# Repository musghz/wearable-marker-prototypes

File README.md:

# wearable-marker-prototypes

Wearable markers for motion capture using a webcam

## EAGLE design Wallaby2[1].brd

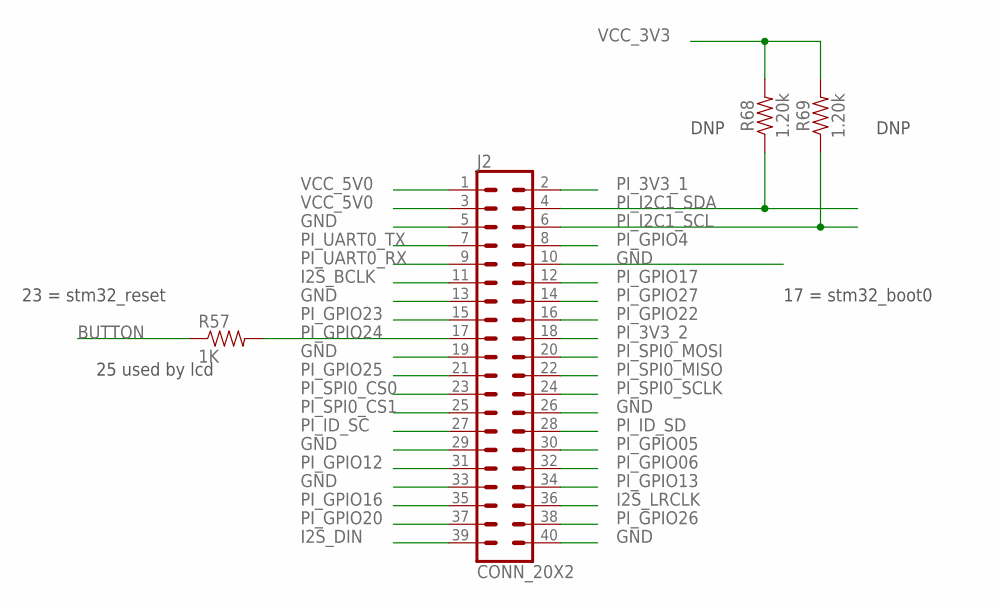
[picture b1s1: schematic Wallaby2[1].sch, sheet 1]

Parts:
J2: CONN_20X2; 2X20
R57: 1K; 0603-RES
R68, R69: 1.20k; 0603

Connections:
BUTTON: R57.1; also elsewhere on the board
GND: J2.5, J2.10, J2.13, J2.19, J2.26, J2.29, J2.33, J2.40; also elsewhere on the board
I2S_BCLK: J2.11; also elsewhere on the board
I2S_DIN: J2.39; also elsewhere on the board
I2S_LRCLK: J2.36; also elsewhere on the board
PI_3V3_1: J2.2
PI_3V3_2: J2.18
PI_GPIO4: J2.8
PI_GPIO05: J2.30
PI_GPIO06: J2.32
PI_GPIO12: J2.31
PI_GPIO13: J2.34
PI_GPIO16: J2.35
PI_GPIO17: J2.12; also elsewhere on the board
PI_GPIO20: J2.37
PI_GPIO22: J2.16
PI_GPIO23: J2.15; also elsewhere on the board
PI_GPIO24: J2.17, R57.2
PI_GPIO25: J2.21; also elsewhere on the board
PI_GPIO26: J2.38
PI_GPIO27: J2.14
PI_I2C1_SCL: J2.6, R69.1; also elsewhere on the board
PI_I2C1_SDA: J2.4, R68.1; also elsewhere on the board
PI_ID_SC: J2.27
PI_ID_SD: J2.28
PI_SPI0_CS0: J2.23; also elsewhere on the board
PI_SPI0_CS1: J2.25
PI_SPI0_MISO: J2.22; also elsewhere on the board
PI_SPI0_MOSI: J2.20; also elsewhere on the board
PI_SPI0_SCLK: J2.24; also elsewhere on the board
PI_UART0_RX: J2.9; also elsewhere on the board
PI_UART0_TX: J2.7; also elsewhere on the board
VCC_3V3: R68.2, R69.2; also elsewhere on the board
VCC_5V0: J2.1, J2.3; also elsewhere on the board

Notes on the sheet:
25 used by lcd
23 = stm32_reset
17 = stm32_boot0
DNP

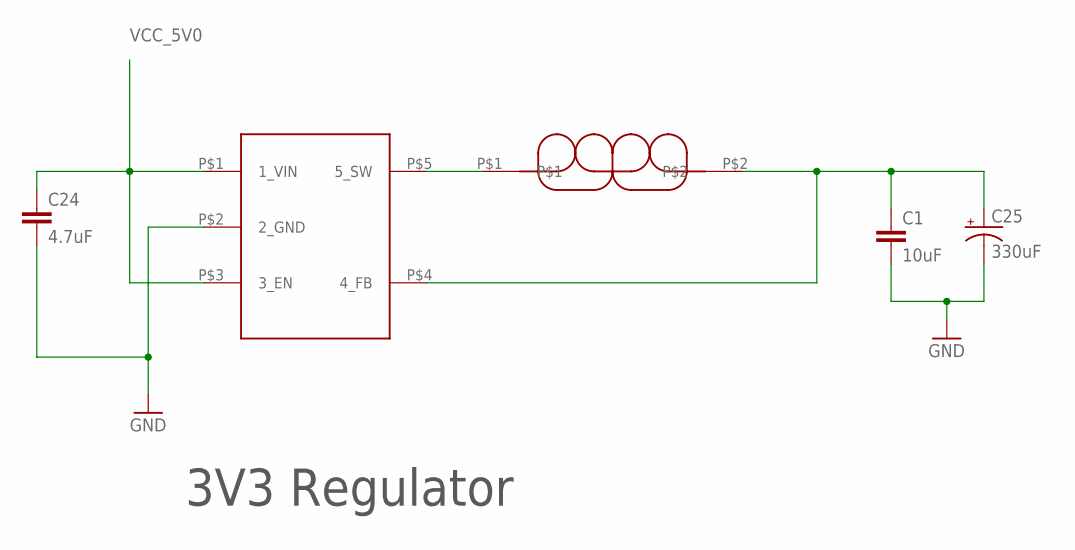
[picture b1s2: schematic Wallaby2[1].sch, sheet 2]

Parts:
C1: 10uF; 0603-CAP
C24: 4.7uF; 0603-CAP
C25: 330uF; PANASONIC_D
U7: LM3671; SOT-23-5
U8: 2.2uH; 3P2MM-X-3P2MM-INDUCTOR

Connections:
GND: C1.2, C24.2, C25.-, U7.P$2 (2_GND); also elsewhere on the board
unnamed: U7.P$5 (5_SW), U8.P$1
VCC_3V3: C1.1, C25.+, U7.P$4 (4_FB), U8.P$2; also elsewhere on the board
VCC_5V0: C24.1, U7.P$1 (1_VIN), U7.P$3 (3_EN); also elsewhere on the board

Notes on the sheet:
3V3 Regulator

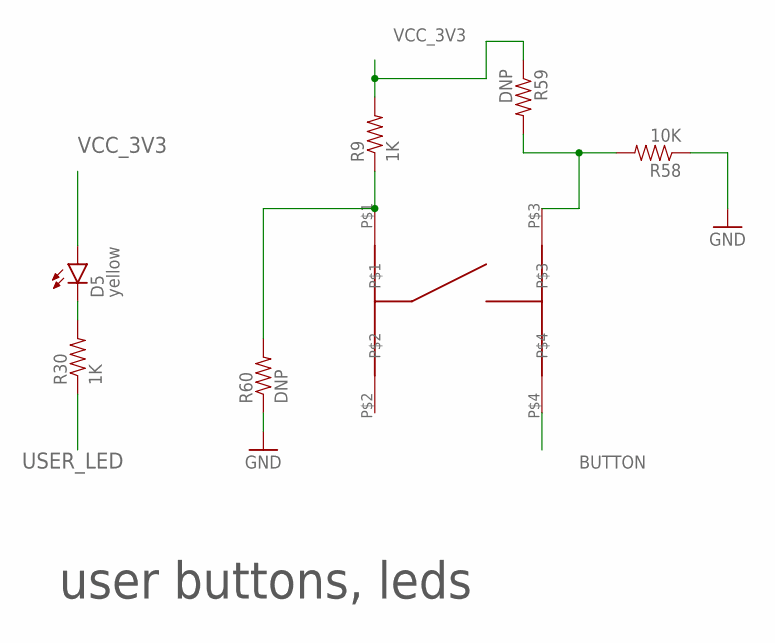
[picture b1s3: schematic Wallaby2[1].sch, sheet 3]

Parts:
D5: yellow; LED-0603
R9, R30: 1K; 0603-RES
R58: 10K; 0603-RES
R59, R60: DNP; 0603-RES
U75: PUSHBUTTON-1571527-2; BUTTON-1571527-2

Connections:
BUTTON: U75.P$4; also elsewhere on the board
GND: R58.1, R60.1; also elsewhere on the board
unnamed: D5.C, R30.2
unnamed: R9.1, R60.2, U75.P$1
unnamed: R58.2, R59.2, U75.P$3
USER_LED: R30.1; also elsewhere on the board
VCC_3V3: D5.A, R9.2, R59.1; also elsewhere on the board

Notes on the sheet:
user buttons, leds

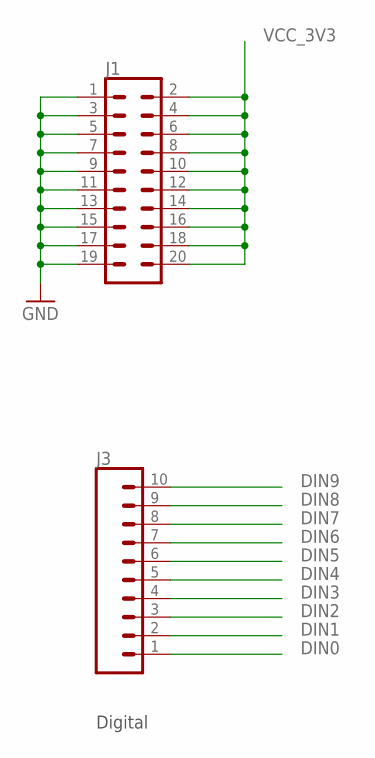
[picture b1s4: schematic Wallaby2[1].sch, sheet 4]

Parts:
J1: CONN_10X2; 2X10
J3: CONN_10"; 1X10

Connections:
DIN0: J3.1; also elsewhere on the board
DIN1: J3.2; also elsewhere on the board
DIN2: J3.3; also elsewhere on the board
DIN3: J3.4; also elsewhere on the board
DIN4: J3.5; also elsewhere on the board
DIN5: J3.6; also elsewhere on the board
DIN6: J3.7; also elsewhere on the board
DIN7: J3.8; also elsewhere on the board
DIN8: J3.9; also elsewhere on the board
DIN9: J3.10; also elsewhere on the board
GND: J1.1, J1.3, J1.5, J1.7, J1.9, J1.11, J1.13, J1.15, J1.17, J1.19; also elsewhere on the board
VCC_3V3: J1.2, J1.4, J1.6, J1.8, J1.10, J1.12, J1.14, J1.16, J1.18, J1.20; also elsewhere on the board

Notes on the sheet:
Digital

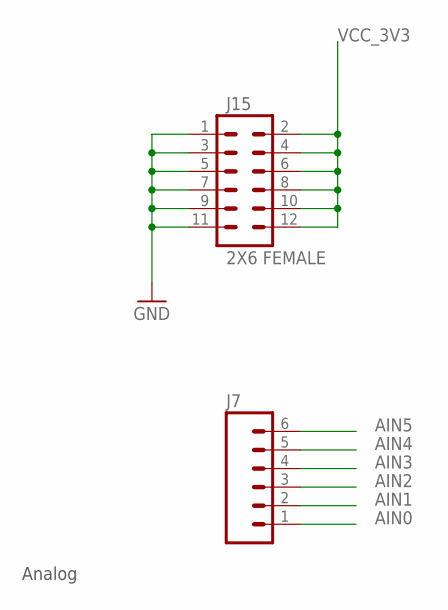
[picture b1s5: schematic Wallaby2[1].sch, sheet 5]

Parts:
J7: M06SILK_FEMALE_PTH; 1X06
J15: 2X6 FEMALE; 2X6

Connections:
AIN0: J7.1; also elsewhere on the board
AIN1: J7.2; also elsewhere on the board
AIN2: J7.3; also elsewhere on the board
AIN3: J7.4; also elsewhere on the board
AIN4: J7.5; also elsewhere on the board
AIN5: J7.6; also elsewhere on the board
GND: J15.1, J15.3, J15.5, J15.7, J15.9, J15.11; also elsewhere on the board
VCC_3V3: J15.2, J15.4, J15.6, J15.8, J15.10, J15.12; also elsewhere on the board

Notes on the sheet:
Analog

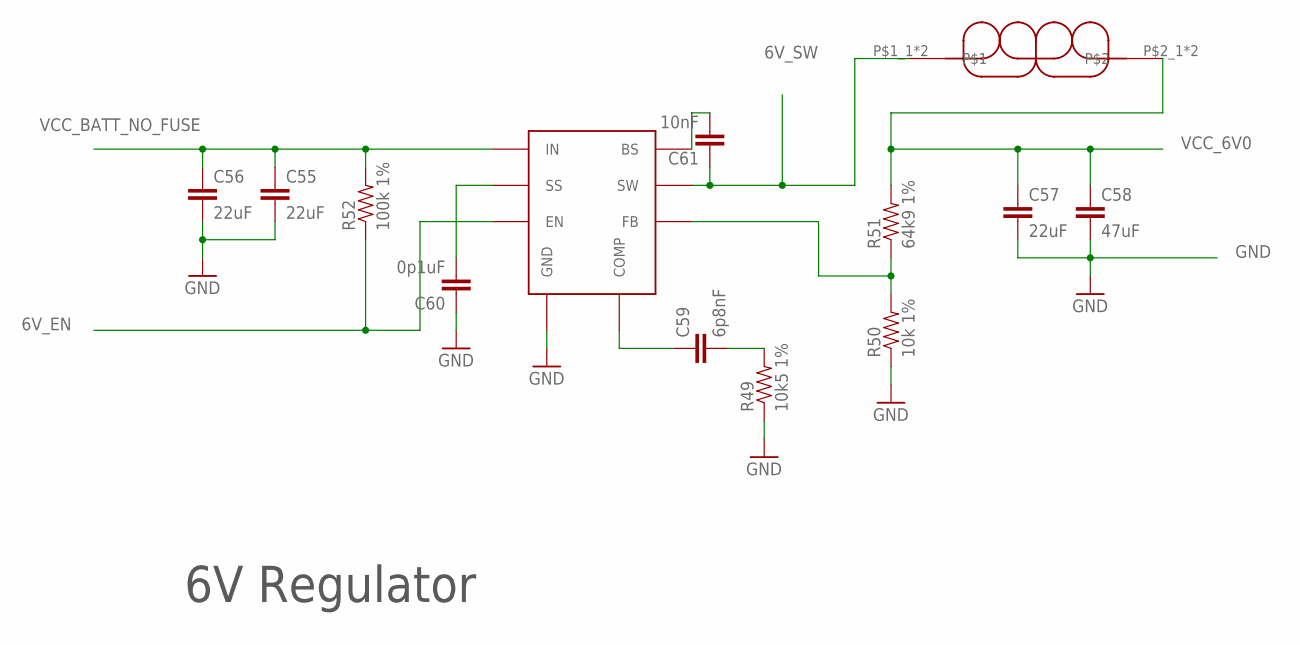
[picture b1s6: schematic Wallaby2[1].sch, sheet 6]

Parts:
C55, C56, C57: 22uF; 1210@1
C58: 47uF; 1210@1
C59: 6p8nF; 0603-CAP
C60: 0p1uF; 0603-CAP
C61: 10nF; 0603-CAP
L2: 6.5uH; INDUCT-3232-1050
R49: 10k5 1%; 0603-RES
R50: 10k 1%; 0603-RES
R51: 64k9 1%; 0603-RES
R52: 100k 1%; 0603-RES
U72: AP65502; SO-8EP

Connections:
6V_EN: R52.1, U72.7 (EN); also elsewhere on the board
6V_SW: C61.1, L2.P$1_1, L2.P$1_2, U72.3 (SW)
GND: C55.2, C56.2, C57.2, C58.2, C60.1, R49.1, R50.1, U72.4 (GND), U72.GND, U72.V$1 (GND), U72.V$2 (GND), U72.V$3 (GND), U72.V$4 (GND), U72.V$5 (GND), U72.V$6 (GND), U72.V$7 (GND), U72.V$8 (GND), U72.V$9 (GND), U72.V$10 (GND), U72.V$11 (GND), U72.V$12 (GND), U72.V$13 (GND), U72.V$14 (GND), U72.V$15 (GND); also elsewhere on the board
unnamed: C61.2, U72.1 (BS)
unnamed: C59.1, U72.6 (COMP)
unnamed: C59.2, R49.2
unnamed: C60.2, U72.8 (SS)
unnamed: R50.2, R51.1, U72.5 (FB)
VCC_6V0: C57.1, C58.1, L2.P$2_1, L2.P$2_2, R51.2; also elsewhere on the board
VCC_BATT_NO_FUSE: C55.1, C56.1, R52.2, U72.2 (IN); also elsewhere on the board

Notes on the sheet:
6V Regulator

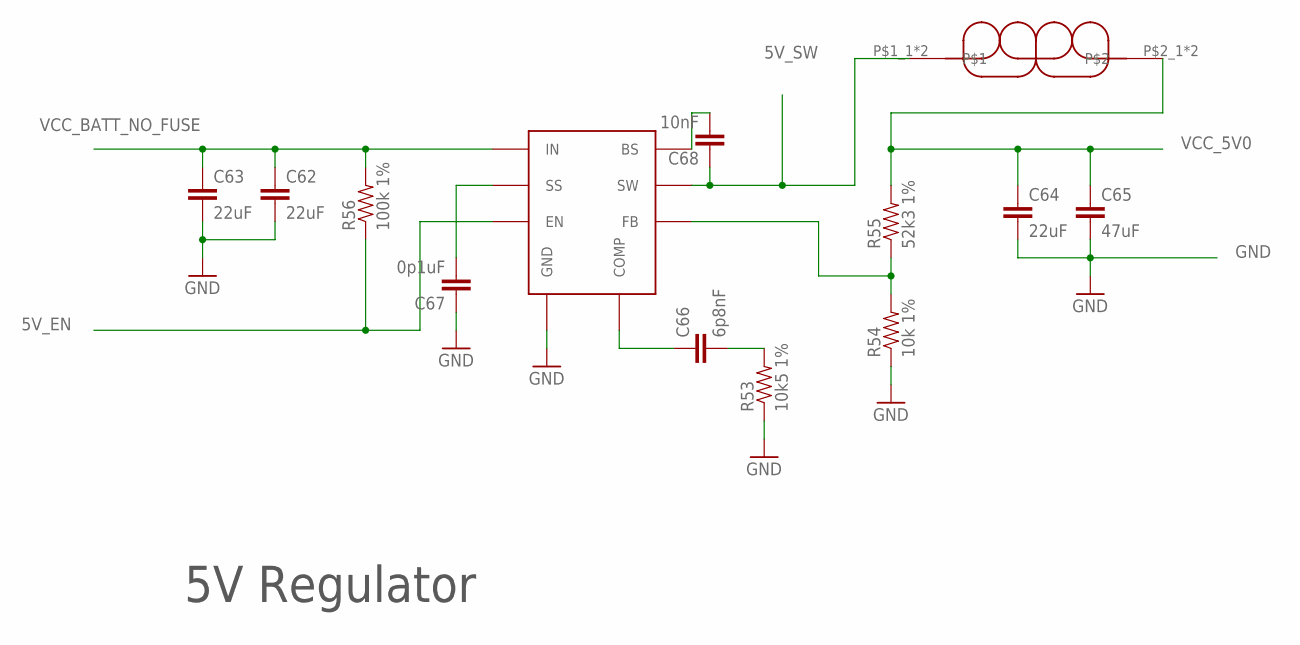
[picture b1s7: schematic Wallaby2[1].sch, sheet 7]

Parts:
C62, C63, C64: 22uF; 1210@1
C65: 47uF; 1210@1
C66: 6p8nF; 0603-CAP
C67: 0p1uF; 0603-CAP
C68: 10nF; 0603-CAP
L4: 6.5uH; INDUCT-3232-1050
R53: 10k5 1%; 0603-RES
R54: 10k 1%; 0603-RES
R55: 52k3 1%; 0603-RES
R56: 100k 1%; 0603-RES
U73: AP65502; SO-8EP

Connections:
5V_EN: R56.1, U73.7 (EN)
5V_SW: C68.1, L4.P$1_1, L4.P$1_2, U73.3 (SW)
GND: C62.2, C63.2, C64.2, C65.2, C67.1, R53.1, R54.1, U73.4 (GND), U73.GND, U73.V$1 (GND), U73.V$2 (GND), U73.V$3 (GND), U73.V$4 (GND), U73.V$5 (GND), U73.V$6 (GND), U73.V$7 (GND), U73.V$8 (GND), U73.V$9 (GND), U73.V$10 (GND), U73.V$11 (GND), U73.V$12 (GND), U73.V$13 (GND), U73.V$14 (GND), U73.V$15 (GND); also elsewhere on the board
unnamed: C68.2, U73.1 (BS)
unnamed: C66.1, U73.6 (COMP)
unnamed: C66.2, R53.2
unnamed: C67.2, U73.8 (SS)
unnamed: R54.2, R55.1, U73.5 (FB)
VCC_5V0: C64.1, C65.1, L4.P$2_1, L4.P$2_2, R55.2; also elsewhere on the board
VCC_BATT_NO_FUSE: C62.1, C63.1, R56.2, U73.2 (IN); also elsewhere on the board

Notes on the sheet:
5V Regulator

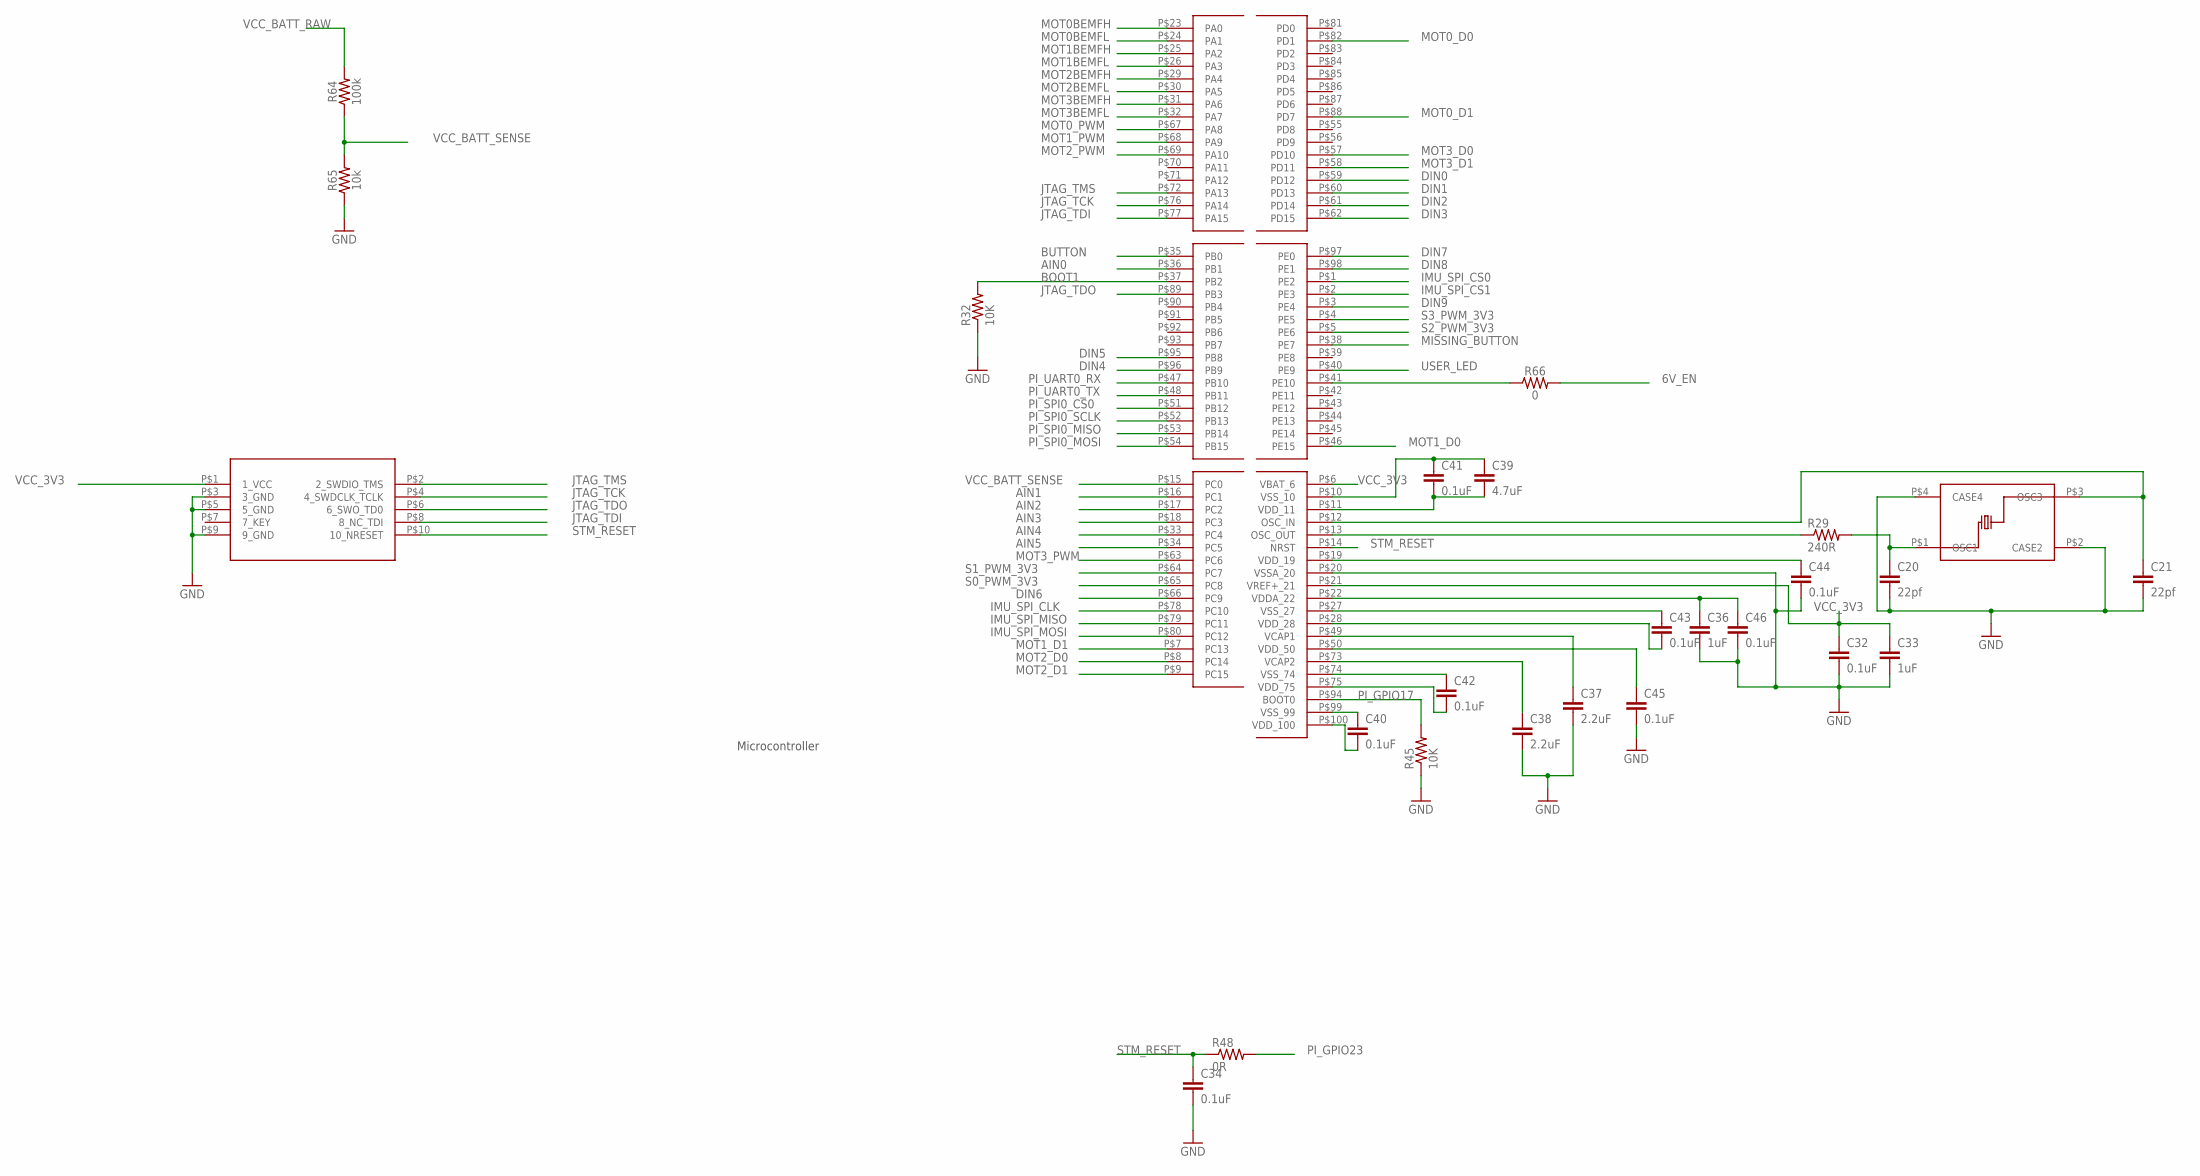
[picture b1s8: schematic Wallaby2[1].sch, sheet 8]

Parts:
C20, C21: 22pf; 0603-CAP
C32, C34, C40, C41, C42, C43, C44, C45, C46: 0.1uF; 0603-CAP
C33, C36: 1uF; 0603-CAP
C37, C38: 2.2uF; 0603-CAP
C39: 4.7uF; 0603-CAP
R29: 240R; 0603-RES
R32, R45: 10K; 0603-RES
R48: 0R; 0603-RES
R64: 100k; 0603
R65: 10k; 0603
R66: 0; 0603
U37: STM32F427VIT6; LQFP-100
U38: TSX-3325; TSX-3225
U39: CORTEX_JTAG; CORTEX-JTAG-HDR

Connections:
6V_EN: R66.2; also elsewhere on the board
AIN0: U37.P$36 (PB1); also elsewhere on the board
AIN1: U37.P$16 (PC1); also elsewhere on the board
AIN2: U37.P$17 (PC2); also elsewhere on the board
AIN3: U37.P$18 (PC3); also elsewhere on the board
AIN4: U37.P$33 (PC4); also elsewhere on the board
AIN5: U37.P$34 (PC5); also elsewhere on the board
BOOT1: R32.2, U37.P$37 (PB2)
BUTTON: U37.P$35 (PB0); also elsewhere on the board
DIN0: U37.P$59 (PD12); also elsewhere on the board
DIN1: U37.P$60 (PD13); also elsewhere on the board
DIN2: U37.P$61 (PD14); also elsewhere on the board
DIN3: U37.P$62 (PD15); also elsewhere on the board
DIN4: U37.P$96 (PB9); also elsewhere on the board
DIN5: U37.P$95 (PB8); also elsewhere on the board
DIN6: U37.P$66 (PC9); also elsewhere on the board
DIN7: U37.P$97 (PE0); also elsewhere on the board
DIN8: U37.P$98 (PE1); also elsewhere on the board
DIN9: U37.P$3 (PE4); also elsewhere on the board
GND: C20.2, C21.2, C32.2, C33.2, C34.2, C36.2, C37.2, C38.2, C39.1, C40.1, C41.1, C42.1, C43.1, C44.2, C45.2, C46.2, R32.1, R45.1, R65.1, U37.P$10 (VSS_10), U37.P$20 (VSSA_20), U37.P$27 (VSS_27), U37.P$74 (VSS_74), U37.P$99 (VSS_99), U38.P$2 (CASE2), U38.P$4 (CASE4), U39.P$3 (3_GND), U39.P$5 (5_GND), U39.P$9 (9_GND); also elsewhere on the board
IMU_SPI_CLK: U37.P$78 (PC10); also elsewhere on the board
IMU_SPI_CS0: U37.P$1 (PE2); also elsewhere on the board
IMU_SPI_CS1: U37.P$2 (PE3)
IMU_SPI_MISO: U37.P$79 (PC11); also elsewhere on the board
IMU_SPI_MOSI: U37.P$80 (PC12); also elsewhere on the board
JTAG_TCK: U37.P$76 (PA14), U39.P$4 (4_SWDCLK_TCLK)
JTAG_TDI: U37.P$77 (PA15), U39.P$8 (8_NC_TDI)
JTAG_TDO: U37.P$89 (PB3), U39.P$6 (6_SWO_TD0)
JTAG_TMS: U37.P$72 (PA13), U39.P$2 (2_SWDIO_TMS)
MISSING_BUTTON: U37.P$38 (PE7)
MOT0BEMFH: U37.P$23 (PA0); also elsewhere on the board
MOT0BEMFL: U37.P$24 (PA1); also elsewhere on the board
MOT0_D0: U37.P$82 (PD1); also elsewhere on the board
MOT0_D1: U37.P$88 (PD7); also elsewhere on the board
MOT0_PWM: U37.P$67 (PA8); also elsewhere on the board
MOT1BEMFH: U37.P$25 (PA2); also elsewhere on the board
MOT1BEMFL: U37.P$26 (PA3); also elsewhere on the board
MOT1_D0: U37.P$46 (PE15); also elsewhere on the board
MOT1_D1: U37.P$7 (PC13); also elsewhere on the board
MOT1_PWM: U37.P$68 (PA9); also elsewhere on the board
MOT2BEMFH: U37.P$29 (PA4); also elsewhere on the board
MOT2BEMFL: U37.P$30 (PA5); also elsewhere on the board
MOT2_D0: U37.P$8 (PC14); also elsewhere on the board
MOT2_D1: U37.P$9 (PC15); also elsewhere on the board
MOT2_PWM: U37.P$69 (PA10); also elsewhere on the board
MOT3BEMFH: U37.P$31 (PA6); also elsewhere on the board
MOT3BEMFL: U37.P$32 (PA7); also elsewhere on the board
MOT3_D0: U37.P$57 (PD10); also elsewhere on the board
MOT3_D1: U37.P$58 (PD11); also elsewhere on the board
MOT3_PWM: U37.P$63 (PC6); also elsewhere on the board
unnamed: C20.1, R29.2, U38.P$1 (OSC1)
unnamed: R66.1, U37.P$41 (PE10)
OSC_IN: C21.1, U37.P$12 (OSC_IN), U38.P$3 (OSC3)
OSC_OUT: R29.1, U37.P$13 (OSC_OUT)
PI_GPIO17: R45.2, U37.P$94 (BOOT0); also elsewhere on the board
PI_GPIO23: R48.2; also elsewhere on the board
PI_SPI0_CS0: U37.P$51 (PB12); also elsewhere on the board
PI_SPI0_MISO: U37.P$53 (PB14); also elsewhere on the board
PI_SPI0_MOSI: U37.P$54 (PB15); also elsewhere on the board
PI_SPI0_SCLK: U37.P$52 (PB13); also elsewhere on the board
PI_UART0_RX: U37.P$47 (PB10); also elsewhere on the board
PI_UART0_TX: U37.P$48 (PB11); also elsewhere on the board
S0_PWM_3V3: U37.P$65 (PC8); also elsewhere on the board
S1_PWM_3V3: U37.P$64 (PC7); also elsewhere on the board
S2_PWM_3V3: U37.P$5 (PE6); also elsewhere on the board
S3_PWM_3V3: U37.P$4 (PE5); also elsewhere on the board
STM_RESET: C34.1, R48.1, U37.P$14 (NRST), U39.P$10 (10_NRESET)
USER_LED: U37.P$40 (PE9); also elsewhere on the board
VCAP1: C37.1, U37.P$49 (VCAP1)
VCAP2: C38.1, U37.P$73 (VCAP2)
VCC_3V3: C32.1, C33.1, C36.1, C39.2, C40.2, C41.2, C42.2, C43.2, C44.1, C45.1, C46.1, U37.P$6 (VBAT_6), U37.P$11 (VDD_11), U37.P$19 (VDD_19), U37.P$21 (VREF+_21), U37.P$22 (VDDA_22), U37.P$28 (VDD_28), U37.P$50 (VDD_50), U37.P$75 (VDD_75), U37.P$100 (VDD_100), U39.P$1 (1_VCC); also elsewhere on the board
VCC_BATT_RAW: R64.2; also elsewhere on the board
VCC_BATT_SENSE: R64.1, R65.2, U37.P$15 (PC0)

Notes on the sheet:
Microcontroller

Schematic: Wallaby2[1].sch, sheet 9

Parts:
C22: 0.1uF; 0603-CAP
R11: 10K; 0603-RES
U42: COINCELL_6P8MM; COIN_CELL_HOLDER_6P8MM
U43: DS1340U; USOP-8
U44: CRYSTAL-ECS-ECX34B; CRYSTAL-ECX34B-3P2MM_1P5MM

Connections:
GND: C22.1, U42.P_MIN, U43.P$4 (4_GND); also elsewhere on the board
unnamed: U42.P_PLUS_1, U42.P_PLUS_2, U43.P$3 (3_VBAT)
unnamed: U43.P$2 (2_X2), U44.P$2
unnamed: U43.P$1 (1_X1), U44.P$1
unnamed: R11.1, U43.P$7 (7_OUT)
PI_I2C1_SCL: U43.P$6 (6_SCL); also elsewhere on the board
PI_I2C1_SDA: U43.P$5 (5_SDA); also elsewhere on the board
VCC_3V3: C22.2, R11.2, U43.P$8 (8_VCC); also elsewhere on the board

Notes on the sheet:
RTC and Battery Backup

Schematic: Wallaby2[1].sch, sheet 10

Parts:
C26, C27: 0.1uF; 0603-CAP
U30, U41, U76, U77: CONN-HEADER-5-103414-1; HEADER-5-103414-1
U56: TXS0104; TSSOP14
U68, U69, U70, U71: FUSE-RESET-0603L100SLYR; 0603

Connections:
GND: C26.2, C27.2, U30.P$3, U41.P$3, U56.P$7 (7_GND), U76.P$3, U77.P$3; also elsewhere on the board
unnamed: U71.P$2, U77.P$2
unnamed: U70.P$2, U76.P$2
unnamed: U30.P$2, U68.P$2
unnamed: U41.P$2, U69.P$2
S0_PWM_3V3: U56.P$5 (5_A4); also elsewhere on the board
S0_PWM_5V0: U30.P$1, U56.P$10 (10_B4)
S1_PWM_3V3: U56.P$4 (4_A3); also elsewhere on the board
S1_PWM_5V0: U41.P$1, U56.P$11 (11_B3)
S2_PWM_3V3: U56.P$3 (3_A2); also elsewhere on the board
S2_PWM_5V0: U56.P$12 (12_B2), U76.P$1
S3_PWM_3V3: U56.P$2 (2_A1); also elsewhere on the board
S3_PWM_5V0: U56.P$13 (13_B1), U77.P$1
VCC_3V3: C27.1, U56.P$1 (1_VCCA), U56.P$8 (8_OE); also elsewhere on the board
VCC_5V0: C26.1, U56.P$14 (14_VCCB); also elsewhere on the board
VCC_6V0: U68.P$1, U69.P$1, U70.P$1, U71.P$1; also elsewhere on the board

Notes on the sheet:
Servos

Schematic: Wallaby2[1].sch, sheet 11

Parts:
C28, C31, C48, C51: 0.1uF 20V; 0603-CAP
C29, C30, C49, C50: 10uF 20V; 0603-CAP
C35, C47, C52, C53: 22pf; 0603-CAP
J8, J10: FEMALE 2x3; 2X3
R12, R13, R28, R31: 1K; 0603-RES
R14, R17, R18, R19, R33, R34, R35, R36: 470R; 0603-RES
R20, R21, R24, R25, R39, R40, R43, R44: 2k2; 0603-RES
R22, R23, R26, R27, R41, R42, R46, R47: 6k8; 0603-RES
U61, U64: TB6612FNG; SSOP24
U62, U63, U65, U66: APB3025ESGC-F01; DUAL_SMT_LED

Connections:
GND: C28.2, C29.2, C30.2, C31.2, C48.2, C49.2, C50.2, C51.2, R17.1, R19.1, R34.1, R36.1, U61.P$3 (PGND1_3), U61.P$4 (PGND1_4), U61.P$9 (PGND2_9), U61.P$10 (PGND2_10), U61.P$18 (GND_18), U64.P$3 (PGND1_3), U64.P$4 (PGND1_4), U64.P$9 (PGND2_9), U64.P$10 (PGND2_10), U64.P$18 (GND_18); also elsewhere on the board
MOT0A: J8.2, J8.4, R26.2, U61.P$1 (AO1_1), U61.P$2 (AO1_2), U63.P$2, U63.P$3
MOT0B: J8.6, R12.1, R27.2, U61.P$5 (AO2_5), U61.P$6 (AO2_6)
MOT0BEMFH: C47.2, R24.2, R26.1; also elsewhere on the board
MOT0BEMFL: C47.1, R25.2, R27.1; also elsewhere on the board
MOT0_D0: U61.P$21 (AIN1_21); also elsewhere on the board
MOT0_D1: U61.P$22 (AIN2_22); also elsewhere on the board
MOT0_PWM: U61.P$23 (PWMA_23); also elsewhere on the board
MOT1A: J8.1, J8.3, R22.2, U61.P$11 (BO1_11), U61.P$12 (BO1_12), U62.P$2, U62.P$3
MOT1B: J8.5, R13.2, R23.2, U61.P$7 (BO2_7), U61.P$8 (BO2_8)
MOT1BEMFH: C35.2, R20.2, R22.1; also elsewhere on the board
MOT1BEMFL: C35.1, R21.2, R23.1; also elsewhere on the board
MOT1_D0: U61.P$17 (BIN1_17); also elsewhere on the board
MOT1_D1: U61.P$16 (BIN2_16); also elsewhere on the board
MOT1_PWM: U61.P$15 (PWMB_15); also elsewhere on the board
MOT2A: J10.2, J10.4, R46.2, U64.P$1 (AO1_1), U64.P$2 (AO1_2), U66.P$2, U66.P$3
MOT2B: J10.6, R28.1, R47.2, U64.P$5 (AO2_5), U64.P$6 (AO2_6)
MOT2BEMFH: C53.2, R43.2, R46.1; also elsewhere on the board
MOT2BEMFL: C53.1, R44.2, R47.1; also elsewhere on the board
MOT2_D0: U64.P$21 (AIN1_21); also elsewhere on the board
MOT2_D1: U64.P$22 (AIN2_22); also elsewhere on the board
MOT2_PWM: U64.P$23 (PWMA_23); also elsewhere on the board
MOT3A: J10.1, J10.3, R41.2, U64.P$11 (BO1_11), U64.P$12 (BO1_12), U65.P$2, U65.P$3
MOT3B: J10.5, R31.2, R42.2, U64.P$7 (BO2_7), U64.P$8 (BO2_8)
MOT3BEMFH: C52.2, R39.2, R41.1; also elsewhere on the board
MOT3BEMFL: C52.1, R40.2, R42.1; also elsewhere on the board
MOT3_D0: U64.P$17 (BIN1_17); also elsewhere on the board
MOT3_D1: U64.P$16 (BIN2_16); also elsewhere on the board
MOT3_PWM: U64.P$15 (PWMB_15); also elsewhere on the board
N22: R13.1, U62.P$1, U62.P$4
N43: R31.1, U65.P$1, U65.P$4
N44: R28.2, U66.P$1, U66.P$4
unnamed: R12.2, U63.P$1, U63.P$4
unnamed: R18.1, R19.2, R20.1, R21.1
unnamed: R14.1, R17.2, R24.1, R25.1
unnamed: R35.1, R36.2, R39.1, R40.1
unnamed: R33.1, R34.2, R43.1, R44.1
VCC_3V3: C30.1, C31.1, C50.1, C51.1, R14.2, R18.2, R33.2, R35.2, U61.P$19 (STBY_19), U61.P$20 (VCC_20), U64.P$19 (STBY_19), U64.P$20 (VCC_20); also elsewhere on the board
VCC_BATT_FUSE: C28.1, C29.1, C48.1, C49.1, U61.P$13 (VM2_13), U61.P$14 (VM3_14), U61.P$24 (VM1_24), U64.P$13 (VM2_13), U64.P$14 (VM3_14), U64.P$24 (VM1_24); also elsewhere on the board

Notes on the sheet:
Motors

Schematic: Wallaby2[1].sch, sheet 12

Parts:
C54: 0.1uF 20V; 0603-CAP
U67: AT24CS01-STUM-T; SOT-23-5

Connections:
GND: C54.2, U67.P$2 (2_GND), U67.P$5 (5_WP); also elsewhere on the board
PI_I2C1_SCL: U67.P$1 (1_SCL); also elsewhere on the board
PI_I2C1_SDA: U67.P$3 (3_SDA); also elsewhere on the board
VCC_3V3: C54.1, U67.P$4 (4_VCC); also elsewhere on the board

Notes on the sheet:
EEPROM Address 0x50

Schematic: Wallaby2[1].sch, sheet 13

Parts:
C69, C70: 0.1uF; 0603
C71: 10pF; 0603
U5: 9DoF IMU; QFN24-3X3

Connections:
GND: C69.2, C70.2, C71.2, U5.11 (FSYNC), U5.18 (GND), U5.20 (GND); also elsewhere on the board
IMU_SPI_CLK: U5.23 (SCL/SCLK); also elsewhere on the board
IMU_SPI_CS0: U5.22 (!CS); also elsewhere on the board
IMU_SPI_MISO: U5.9 (AD0/SDO); also elsewhere on the board
IMU_SPI_MOSI: U5.24 (SDA/SDI); also elsewhere on the board
unnamed: C70.1, U5.10 (REGOUT)
unnamed: C71.1, U5.1 (VDDIO), U5.8 (VDDIO)
VCC_3V3: C69.1, U5.13 (VDD); also elsewhere on the board

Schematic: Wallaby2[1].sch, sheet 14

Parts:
D4: red; LED-0603
Q1, Q2: BSP170P; SOT223
R10: 1K; 0603-RES
R37: 3K3; 0603-RES
R38: 100K; 0603-RES
U3: XT60; XT60-FP-MH
U35: SWITCH-OS102011MA1QN1; OS-SPDT-MINI-SLIDE_SWITCH
U74: 2920L500-16MR; FUSE-2920

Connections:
GND: R10.1, U3.NEG (CONN_N), U35.P$1; also elsewhere on the board
unnamed: D4.C, R10.2
unnamed: R37.2, U35.P$2
unnamed: Q1.1 (G), Q2.1 (G), R37.1, R38.2
VCC_BATT_FUSE: U74.P$2; also elsewhere on the board
VCC_BATT_NO_FUSE: D4.A, Q1.2 (D), Q1.4 (D); also elsewhere on the board
VCC_BATT_PRE_FUSE: Q2.2 (D), Q2.4 (D), U74.P$1
VCC_BATT_RAW: Q1.3 (S), Q2.3 (S), R38.1, U3.POS (CONN_P); also elsewhere on the board

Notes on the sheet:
Power

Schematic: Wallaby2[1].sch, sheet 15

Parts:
C14: 10uF; 0603
C15: 0.1uF; 0603
C23, C72: 22pF; 0603
FB5, FB6: Ferrite; _0805MP
J4: CONN_02; 1X02
R61: 1M; 0603
R62, R63: DNP; 0603
U45: MAX98357; TQFN-16

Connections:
GND: C14.2, C15.2, C23.2, C72.2, R63.1, U45.GND, U45.P$3 (GND), U45.P$11 (GND), U45.P$15 (GND); also elsewhere on the board
I2S_BCLK: U45.P$16 (BCLK); also elsewhere on the board
I2S_DIN: U45.P$1 (DIN); also elsewhere on the board
I2S_LRCLK: U45.P$14 (LRCLK); also elsewhere on the board
unnamed: FB5.1, U45.P$9 (OUTP)
unnamed: FB6.1, U45.P$10 (OUTN)
unnamed: C23.1, FB5.2, J4.1
unnamed: C72.1, FB6.2, J4.2
unnamed: R61.1, U45.P$4 (SD)
unnamed: R62.1, R63.2, U45.P$2 (GAIN)
VCC_5V0: C14.1, C15.1, R61.2, R62.2, U45.P$7 (VDD), U45.P$8 (VDD); also elsewhere on the board

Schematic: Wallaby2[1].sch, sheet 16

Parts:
C2, C3, C4, C5, C6, C7, C8, C9, C10, C11, C13, C19, C74: 0.1uF; 0603
C12, C73: 2.2uF; 0603
C16: 10uF; 0805-NO
C17, C18: 1uF; 0805-NO
D1: MBR0540; SOD-123
D2: MM3Z24VT1G; SMADIODE
D3: 1N4148; SOD-323
FB1, FB2, FB3, FB4: Ferrite; _0805MP
J9: 40PINFPCM4-1734839-0; 4-1734839-0
L1: 15uH; INDUCTOR_5X5MM_NR5040_NOTHERMALS
R1, R2, R3, R4, R5, R8: 10k; 0603
R6, R67, R70, R71, R72, R73: 0; 0603
R7: 47k; 0603
R15, R16: 12; 0805-NO
SJ1, SJ2: SOLDERJUMPER; SOLDERJUMPER_ARROW_NOPASTE
SJ3: -25mA; SOLDERJUMPER_CLOSEDWIRE
U1: TFP401; S-PQFP-G100
U2: 24LC02BT-I/OT; SOT23-5
U4: FAN5333BSX; SOT23-5
U31, U32, U33, U34: MOUNTINGHOLE3.0; MOUNTINGHOLE_3.0_PLATED
U$8: TSC2003; TSSOP16
X1: 47151-0001; HDMI_MOLEX_47151-0001_DIMLAYER

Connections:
5.0V: C13.1, R1.1, R3.2, R4.2, U2.4 (VCC), X1.18 (+5V)
24V: C17.1, C18.1, D1.C, D2.C, J9.2 (MS)
ACTIVE: D3.C, J9.31 (MS), U1.8 (SCDT)
AVDD: C9.1, C11.1, FB3.2, U1.82 (AVDD), U1.84 (AVDD), U1.88 (AVDD), U1.95 (AVDD)
B0: J9.21 (MS), U1.10 (QE0)
B1: J9.22 (MS), U1.11 (QE1)
B2: J9.23 (MS), U1.12 (QE2)
B3: J9.24 (MS), U1.13 (QE3)
B4: J9.25 (MS), U1.14 (QE4)
B5: J9.26 (MS), U1.15 (QE5)
B6: J9.27 (MS), U1.16 (QE6)
B7: J9.28 (MS), U1.17 (QE7)
CTL1: U1.40 (CTL1)
CTL2: U1.41 (CTL2)
CTL3: U1.42 (CTL3)
DISPEN: J9.34 (MS), U1.46 (DE)
G0: J9.13 (MS), U1.20 (QE8)
G1: J9.14 (MS), U1.21 (QE9)
G2: J9.15 (MS), U1.22 (QE10)
G3: J9.16 (MS), U1.23 (QE11)
G4: J9.17 (MS), U1.24 (QE12)
G5: J9.18 (MS), U1.25 (QE13)
G6: J9.19 (MS), U1.26 (QE14)
G7: J9.20 (MS), U1.27 (QE15)
GND: C2.2, C3.2, C4.2, C5.2, C6.2, C7.2, C8.2, C9.2, C10.2, C11.2, C12.2, C13.2, C16.1, C17.2, C18.2, C19.2, C73.2, C74.2, J9.3 (MS), J9.29 (MS), J9.36 (MS), R5.1, R15.2, R16.2, R72.2, R73.2, SJ2.1, U1.1 (DFO), U1.4 (PIXS), U1.5 (GND), U1.19 (OGND), U1.28 (OGND), U1.39 (GND), U1.45 (OGND), U1.58 (OGND), U1.68 (GND), U1.76 (OGND), U1.79 (AGND), U1.83 (AGND), U1.87 (AGND), U1.89 (AGND), U1.92 (AGND), U1.98 (PGND), U1.P$1 (TP), U1.P$2 (TP), U1.P$3 (TP), U1.P$4 (TP), U1.P$5 (TP), U1.P$6 (TP), U1.P$7 (TP), U1.P$8 (TP), U1.P$9 (TP), U1.P$10 (TP), U1.P$11 (TP), U1.P$12 (TP), U1.P$13 (TP), U1.P$14 (TP), U1.P$15 (TP), U1.P$16 (TP), U1.THERMAL (TP), U2.2 (GND), U2.5 (WP), U4.2 (GND), U$8.P$6 (6_GND), X1.2 (TX2_SHIELD), X1.5 (TX1_SHIELD), X1.8 (TX0_SHIELD), X1.11 (TXC_SHIELD), X1.17 (GND), X1.P$1 (GND), X1.P$2 (GND), X1.P$3 (GND), X1.P$4 (GND); also elsewhere on the board
HSYNC: J9.32 (MS), U1.48 (HSYNC)
LEDK: C19.1, D2.A, J9.1 (MSV), R16.1, SJ3.2, U4.3 (FB)
unnamed: U1.93 (RXC+), X1.10 (TXC+)
unnamed: U1.94 (RXC-), X1.12 (TXC-)
unnamed: U1.90 (RX0+), X1.7 (TX0+)
unnamed: U1.91 (RX0-), X1.9 (TX0-)
unnamed: U1.85 (RX1+), X1.4 (TX1+)
unnamed: U1.86 (RX1-), X1.6 (TX1-)
unnamed: U1.80 (RX2+), X1.1 (TX2+)
unnamed: U1.81 (RX2-), X1.3 (TX2-)
unnamed: R1.2, X1.19 (HOTPLUG)
unnamed: R67.1, U$8.P$7 (7_VBAT1)
unnamed: C73.1, C74.1, R6.2, U$8.P$9 (9_VREF)
unnamed: R71.2, R73.1, U$8.P$13 (13_A1)
unnamed: D1.A, L1.P$2 (2), U4.1 (SW)
unnamed: R15.1, SJ3.1
unnamed: D3.A, R8.1, U4.4 (SHDN)
unnamed: R70.2, R72.1, U$8.P$14 (14_A0)
OCK_INV: R5.2, SJ1.1, U1.100 (OCK_INV)
OVDD: C5.1, C6.1, C7.1, C8.1, FB2.2, U1.18 (OVDD), U1.29 (OVDD), U1.43 (OVDD), U1.57 (OVDD), U1.78 (OVDD)
PIXCLK: J9.30 (MS), U1.44 (ODCK)
PI_GPIO25: R7.2, U$8.P$10 (10_PEN); also elsewhere on the board
PI_I2C1_SCL: U$8.P$12 (12_SCL); also elsewhere on the board
PI_I2C1_SDA: U$8.P$11 (11_SDA); also elsewhere on the board
PVDD: C10.1, FB4.2, U1.97 (PVDD)
PWRDN: U1.2 (#PD)
PWRDN_O: U1.9 (#PDO)
R0: J9.5 (MS), U1.30 (QE16)
R1: J9.6 (MS), U1.31 (QE17)
R2: J9.7 (MS), U1.32 (QE18)
R3: J9.8 (MS), U1.33 (QE19)
R4: J9.9 (MS), U1.34 (QE20)
R5: J9.10 (MS), U1.35 (QE21)
R6: J9.11 (MS), U1.36 (QE22)
R7: J9.12 (MS), U1.37 (QE23)
SCL: R4.1, U2.1 (SCL), X1.15 (DCLK)
SDA: R3.1, U2.3 (SDA), X1.16 (DDAT)
ST: R2.1, SJ2.2, U1.3 (ST)
VCC_3V3: C4.1, C12.1, FB1.1, FB2.1, FB3.1, FB4.1, J9.4 (MS), R6.1, R7.1, R67.2, R70.1, R71.1, U$8.P$1 (1_VDD); also elsewhere on the board
VCC_5V0: C16.2, L1.P$1 (1), R8.2, U4.5 (VIN); also elsewhere on the board
VDDIO: C2.1, C3.1, FB1.2, R2.2, SJ1.2, U1.6 (DVDD), U1.7 (#STAG), U1.38 (DVDD), U1.67 (DVDD), U1.99 (RSVD)
VSYNC: J9.33 (MS), U1.47 (VSYNC)
X+: J9.37 (MS), U$8.P$2 (2_XP)
X-: J9.39 (MS), U$8.P$4 (4_XN)
Y+: J9.38 (MS), U$8.P$3 (3_YP)
Y-: J9.40 (MS), U$8.P$5 (5_XP)

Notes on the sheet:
DNP

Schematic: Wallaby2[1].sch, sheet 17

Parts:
FID1, FID2, FID3, FID4, FID5, FID6: FIDUCIAL1X2.5; FIDUCIAL-1X2.5

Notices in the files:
parts and their libraries:
microbuilder: This work is placed in the public domain, and may be freely used for commercial and non-commercial work with the following conditions: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
SparkFun-Capacitors: Licensing: Creative Commons ShareAlike 4.0 International - https://creativecommons.org/licenses/by-sa/4.0
